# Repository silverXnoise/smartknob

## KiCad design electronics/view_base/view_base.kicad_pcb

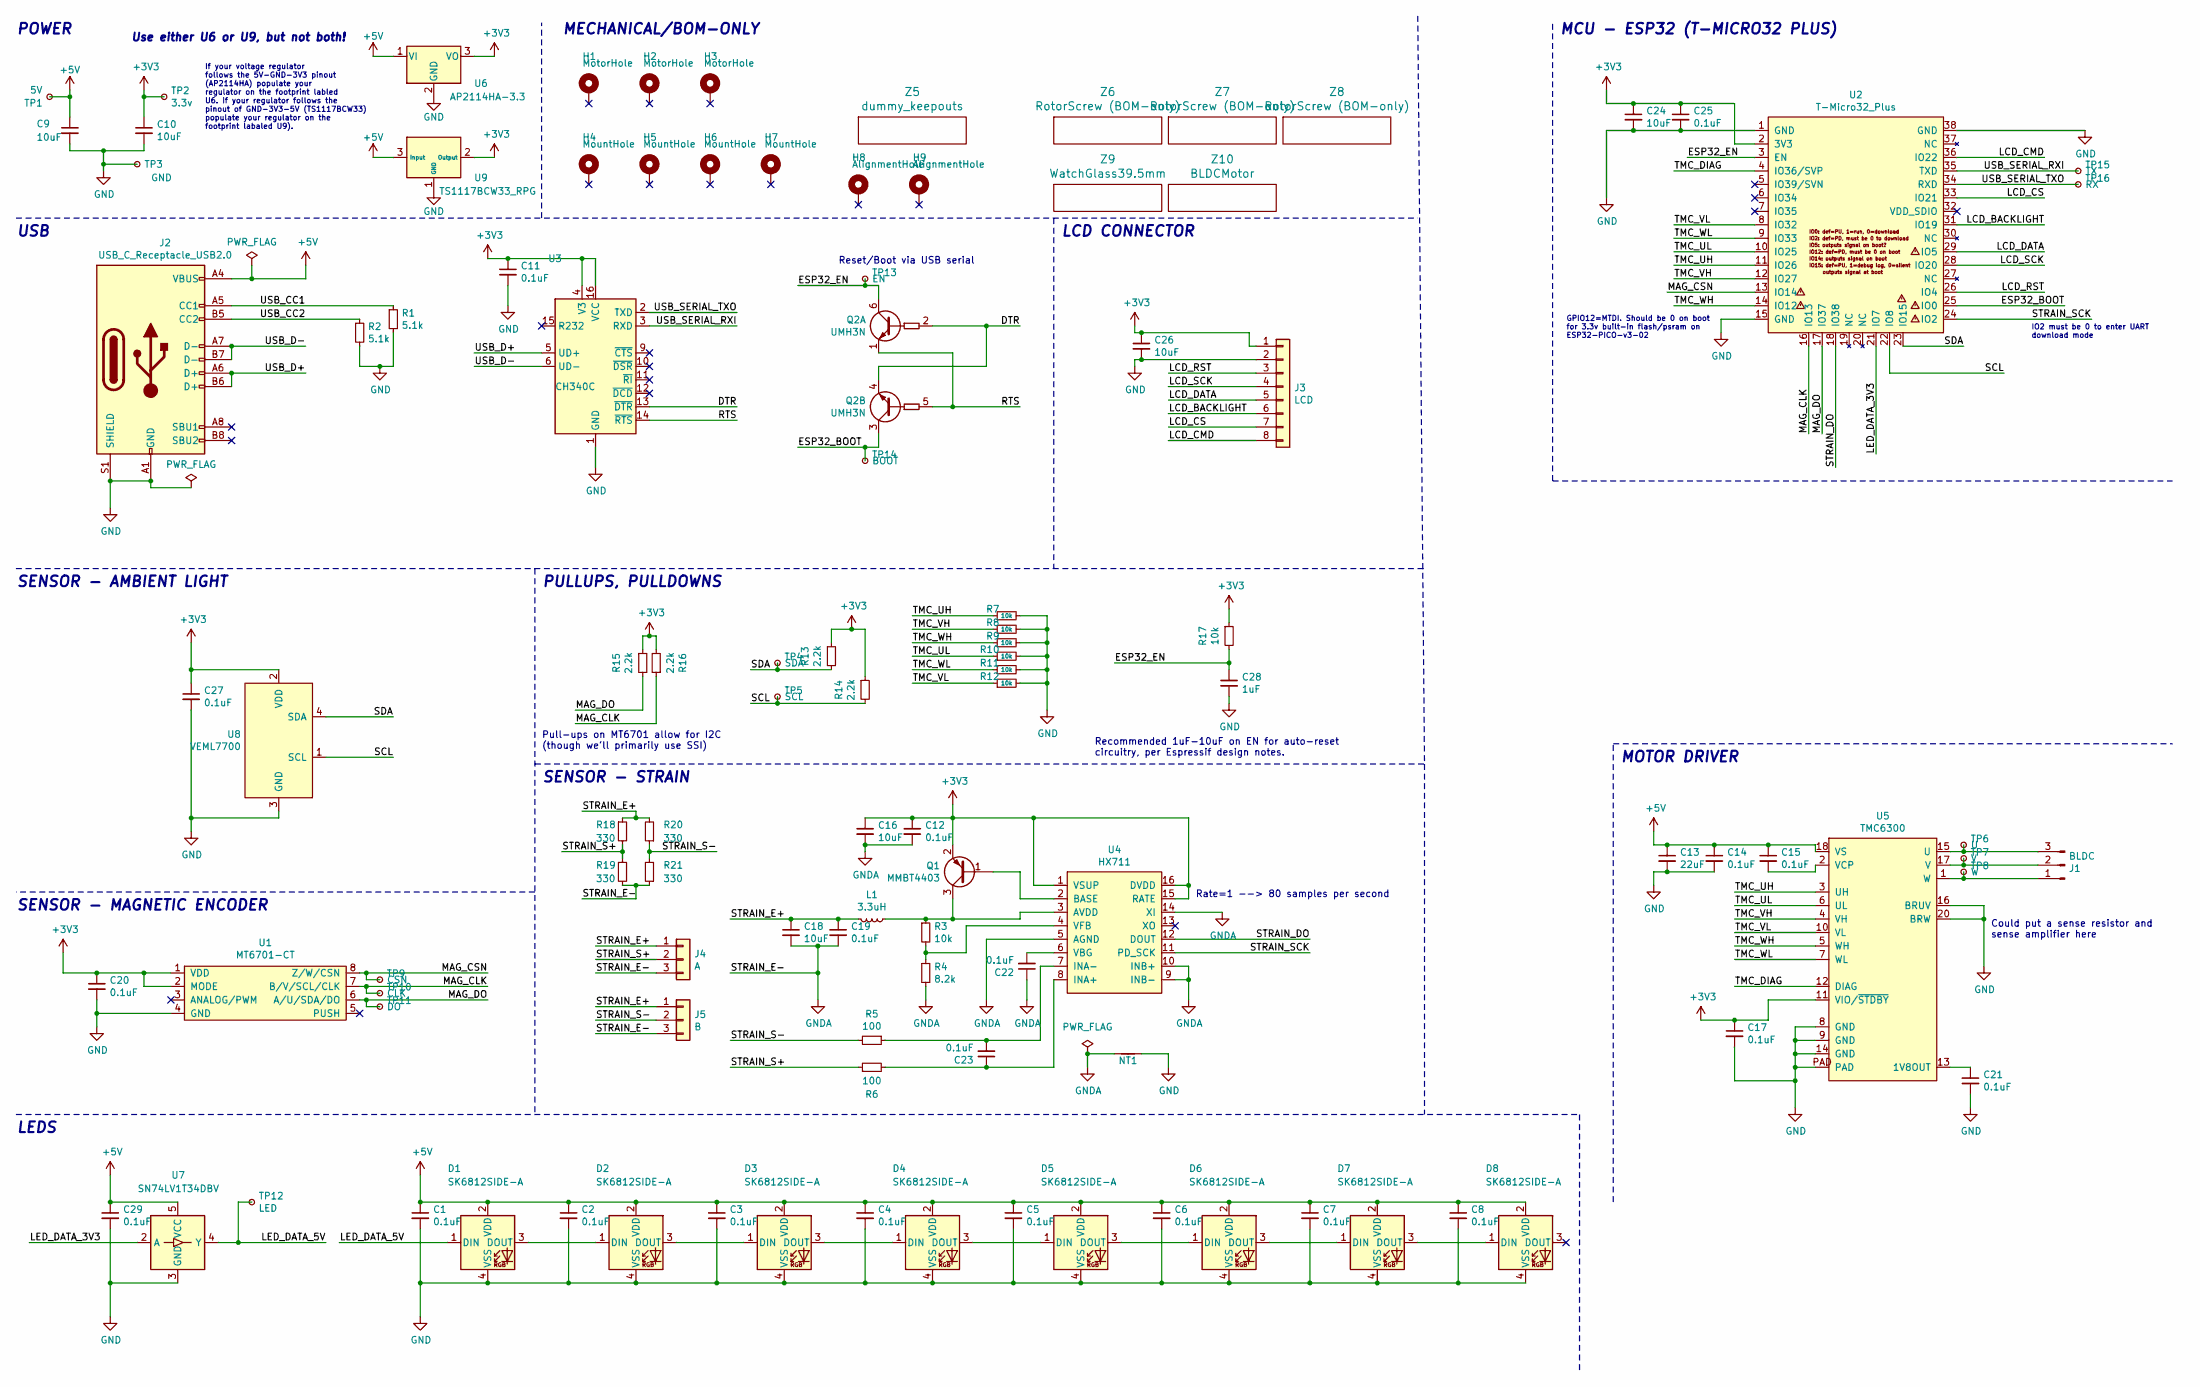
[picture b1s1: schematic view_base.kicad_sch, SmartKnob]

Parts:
C1, C2, C3, C4, C5, C6, C7, C8, C11, C12, C14, C15, C17, C19, C20, C21, C22, C23, C25, C27, C29: 0.1uF; C_0603_1608Metric; LCSC C1591
C9, C10, C16, C18, C24, C26: 10uF; C_0805_2012Metric; LCSC C2922480
C13: 22uF; C_0805_2012Metric; LCSC C98190
C28: 1uF; C_0603_1608Metric; Mouser 187-CL10A105KA8NNNC
D1, D2, D3, D4, D5, D6, D7, D8: SK6812SIDE-A; SK6812-SIDE-A; Digikey 1528-4691-ND
H1, H2, H3: MotorHole; MountingHole_M1.6; LCSC C2931389
H4, H5, H6, H7: MountHole; MountingHole_2.2mm_M2_ISO7380_Pad_NonVirtual; LCSC C2911210 or C2911532 (screw), C2961595 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
H8, H9: AlignmentHole; MountingHole_2.2mm_M2_ISO7380_Pad_NonVirtual
J1: BLDC; 532610371; LCSC C293630
J2: USB_C_Receptacle_USB2.0; USB4510_NoPaste; LCSC C428463
J3: LCD; SolderPads_2mm_8
J4: A; SolderPads_2mm_3_STRAIN
J5: B; SolderPads_2mm_3_STRAIN
L1: 3.3uH; L_0805_2012Metric; LCSC C307744
NT1: NetTie_2; NetTie-2_SMD_Pad0.5mm
Q1: MMBT4403; SOT-23; LCSC C78864
Q2: UMH3N; SOT-363_SC-70-6; LCSC C62892
R1, R2: 5.1k; R_0603_1608Metric; LCSC C105580
R3, R7, R8, R9, R10, R11, R12, R17: 10k; R_0603_1608Metric; LCSC C98220
R4: 8.2k; R_0603_1608Metric; LCSC C114637
R5, R6: 100; R_0603_1608Metric; LCSC C319953
R13, R14, R15, R16: 2.2k; R_0603_1608Metric; LCSC C4190
R18, R19, R20, R21: 330; R_2512_6332Metric; LCSC C19866
TP1: 5V; TestPoint_Pad_D2.0mm_ValueSilk
TP2: 3.3v; TestPoint_Pad_D2.0mm_ValueSilk
TP3: GND; TestPoint_Pad_D2.0mm_ValueSilk
TP4: SDA; TestPoint_Pad_D2.0mm_ValueSilk
TP5: SCL; TestPoint_Pad_D2.0mm_ValueSilk
TP6: U; TestPoint_Pad_D2.0mm_ValueSilk
TP7: V; TestPoint_Pad_D2.0mm_ValueSilk
TP8: W; TestPoint_Pad_D2.0mm_ValueSilk
TP9: CSN; TestPoint_Pad_D2.0mm_ValueSilk
TP10: CLK; TestPoint_Pad_D2.0mm_ValueSilk
TP11: DO; TestPoint_Pad_D2.0mm_ValueSilk
TP12: LED; TestPoint_Pad_D2.0mm_ValueSilk
TP13: EN; TestPoint_Pad_D2.0mm_ValueSilk
TP14: BOOT; TestPoint_Pad_D2.0mm_ValueSilk
TP15: TX; TestPoint_Pad_D2.0mm_ValueSilk
TP16: RX; TestPoint_Pad_D2.0mm_ValueSilk
U1: MT6701-CT; SOIC-8_3.9x4.9mm_P1.27mm; LCSC C2856764, or C3003196
U2: T-Micro32_Plus; T-Micro32; Digikey N/A
U3: CH340C; SOIC-16_3.9x9.9mm_P1.27mm; LCSC C84681
U4: HX711; SOIC-16_3.9x9.9mm_P1.27mm; LCSC C43656
U5: TMC6300; QFN-20-1EP_3x3mm_P0.4mm_EP1.65x1.65mm_ThermalVias_LargerVia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; Digikey TMC6300-LA-T
U6: AP2114HA-3.3; SOT-223-3_TabPin2_InGndOut; LCSC C460314
U7: SN74LV1T34DBV; SOT-23-5; LCSC C100024
U8: VEML7700; VEML7700-TOP; Digikey VEML7700-TT
U9: TS1117BCW33_RPG; SOT-223-3_TabPin2_GndOutIn; LCSC C6186, C35879, or others
Z5: dummy_keepouts; ViewKeepouts3d
Z6, Z7, Z8: RotorScrew (BOM-only); bom_only_no_pin
Z9: WatchGlass39.5mm; bom_only_no_pin
Z10: BLDCMotor; bom_only_no_pin

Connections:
+3V3: C10.1, C11.1, C12.1, C16.1, C17.1, C20.1, C24.1, C25.1, C26.1, C27.1, J3.1, Q1.2 (E), R13.1, R14.1, R15.1, R16.2, R17.1, TP2.1, U1.1 (VDD), U1.2 (MODE), U2.2 (3V3), U3.4 (V3), U3.16 (VCC), U4.1 (VSUP), U4.15 (RATE), U4.16 (DVDD), U5.11 (VIO/~STDBY), U6.3 (VO), U8.2 (VDD), U9.2 (Output)
+5V: C1.1, C2.1, C3.1, C4.1, C5.1, C6.1, C7.1, C8.1, C9.1, C13.1, C14.1, C15.1, C29.1, D1.2 (VDD), D2.2 (VDD), D3.2 (VDD), D4.2 (VDD), D5.2 (VDD), D6.2 (VDD), D7.2 (VDD), D8.2 (VDD), J2.A4 (VBUS), J2.A9 (VBUS), J2.B4 (VBUS), J2.B9 (VBUS), TP1.1, U5.18 (VS), U6.1 (VI), U7.5 (VCC), U9.3 (Input)
/DTR: Q2.2 (B1), Q2.4 (E2), U3.13 (~DTR)
/ESP32_BOOT: Q2.3 (C2), TP14.1, U2.25 (IO0)
/ESP32_EN: C28.1, Q2.6 (C1), R17.2, TP13.1, U2.3 (EN)
/LCD_BACKLIGHT: J3.6, U2.31 (IO19)
/LCD_CMD: J3.8, U2.36 (IO22)
/LCD_CS: J3.7, U2.33 (IO21)
/LCD_DATA: J3.5, U2.29 (IO5)
/LCD_RST: J3.3, U2.26 (IO4)
/LCD_SCK: J3.4, U2.28 (IO20)
/LED_DATA_3V3: U2.21 (IO7), U7.2 (A)
/LED_DATA_5V: D1.1 (DIN), TP12.1, U7.4 (Y)
/MAG_CLK: R16.1, TP10.1, U1.7 (B/V/SCL/CLK), U2.16 (IO13)
/MAG_CSN: TP9.1, U1.8 (Z/W/CSN), U2.13 (IO14)
/MAG_DO: R15.2, TP11.1, U1.6 (A/U/SDA/DO), U2.17 (IO37)
/RTS: Q2.1 (E1), Q2.5 (B2), U3.14 (~RTS)
/SCL: R14.2, TP5.1, U2.22 (IO8), U8.1 (SCL)
/SDA: R13.2, TP4.1, U2.23 (IO15), U8.4 (SDA)
/STRAIN_DO: U2.18 (IO38), U4.12 (DOUT)
/STRAIN_E+: C18.1, C19.1, J4.1, J5.1, L1.2, R18.1, R20.2
/STRAIN_S+: J4.2, R6.1, R18.2, R19.1
/STRAIN_S-: J5.2, R5.2, R20.1, R21.2
/STRAIN_SCK: U2.24 (IO2), U4.11 (PD_SCK)
/TMC_DIAG: U2.4 (IO36/SVP), U5.12 (DIAG)
/TMC_UH: R7.1, U2.11 (IO26), U5.3 (UH)
/TMC_UL: R10.1, U2.10 (IO25), U5.6 (UL)
/TMC_VH: R8.1, U2.12 (IO27), U5.4 (VH)
/TMC_VL: R12.1, U2.8 (IO32), U5.10 (VL)
/TMC_WH: R9.1, U2.14 (IO12), U5.5 (WH)
/TMC_WL: R11.1, U2.9 (IO33), U5.7 (WL)
/USB_CC1: J2.A5 (CC1), R1.1
/USB_CC2: J2.B5 (CC2), R2.1
/USB_D+: J2.A6 (D+), J2.B6 (D+), U3.5 (UD+)
/USB_D-: J2.A7 (D-), J2.B7 (D-), U3.6 (UD-)
/USB_SERIAL_RXI: TP15.1, U2.35 (TXD), U3.3 (RXD)
/USB_SERIAL_TXO: TP16.1, U2.34 (RXD), U3.2 (TXD)
GND: C1.2, C2.2, C3.2, C4.2, C5.2, C6.2, C7.2, C8.2, C9.2, C10.2, C11.2, C13.2, C14.2, C17.2, C20.2, C21.2, C24.2, C25.2, C26.2, C27.2, C28.2, C29.2, D1.4 (VSS), D2.4 (VSS), D3.4 (VSS), D4.4 (VSS), D5.4 (VSS), D6.4 (VSS), D7.4 (VSS), D8.4 (VSS), J2.A1 (GND), J2.A12 (GND), J2.B1 (GND), J2.B12 (GND), J2.S1 (SHIELD), J3.2, NT1.2, R1.2, R2.2, R7.2, R8.2, R9.2, R10.2, R11.2, R12.2, TP3.1, U1.4 (GND), U2.1 (GND), U2.15 (GND), U2.38 (GND), U3.1 (GND), U5.8 (GND), U5.9 (GND), U5.14 (GND), U5.16 (BRUV), U5.20 (BRW), U5.PAD, U6.2 (GND), U7.3 (GND), U8.3 (GND), U9.1 (GND)
GNDA: C12.2, C16.2, C18.2, C19.2, C22.1, J4.3, J5.3, NT1.1, R4.2, R19.2, R21.1, U4.5 (AGND), U4.9 (INB-), U4.10 (INB+), U4.14 (XI)
unnamed: D1.3 (DOUT), D2.1 (DIN)
unnamed: D2.3 (DOUT), D3.1 (DIN)
unnamed: D3.3 (DOUT), D4.1 (DIN)
unnamed: D4.3 (DOUT), D5.1 (DIN)
unnamed: D5.3 (DOUT), D6.1 (DIN)
unnamed: D6.3 (DOUT), D7.1 (DIN)
unnamed: D7.3 (DOUT), D8.1 (DIN)
unnamed: J1.1, TP8.1, U5.1 (W)
unnamed: J1.2, TP7.1, U5.17 (V)
unnamed: J1.3, TP6.1, U5.15 (U)
unnamed: Q1.1 (B), U4.2 (BASE)
unnamed: L1.1, Q1.3 (C), R3.1, U4.3 (AVDD)
unnamed: C23.1, R6.2, U4.8 (INA+)
unnamed: C23.2, R5.1, U4.7 (INA-)
unnamed: C22.2, U4.6 (VBG)
unnamed: R3.2, R4.1, U4.4 (VFB)
unnamed: C21.1, U5.13 (1V8OUT)
unnamed: C15.2, U5.2 (VCP)

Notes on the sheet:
POWER
Could put a sense resistor and sense amplifier here
MCU - ESP32 (T-MICRO32 PLUS)
If your voltage regulator follows the 5V-GND-3V3 pinout (AP2114HA) populate your regulator on the footprint labled U6. If your regulator follows the pinout of GND-3V3-5V (TS1117BCW33) populate your regulator on the footprint labaled U9).
SENSOR - MAGNETIC ENCODER
MOTOR DRIVER
MECHANICAL/BOM-ONLY
IO2 must be 0 to enter UART download mode
GPIO12=MTDI. Should be 0 on boot for 3.3v built-in flash/psram on ESP32-PICO-v3-02
Pull-ups on MT6701 allow for I2C (though we'll primarily use SSI)
Use either U6 or U9, but not both!
Rate=1 --> 80 samples per second
SENSOR - AMBIENT LIGHT
Recommended 1uF-10uF on EN for auto-reset circuitry, per Espressif design notes.
USB
SENSOR - STRAIN
LEDS
PULLUPS, PULLDOWNS
LCD CONNECTOR
Reset/Boot via USB serial

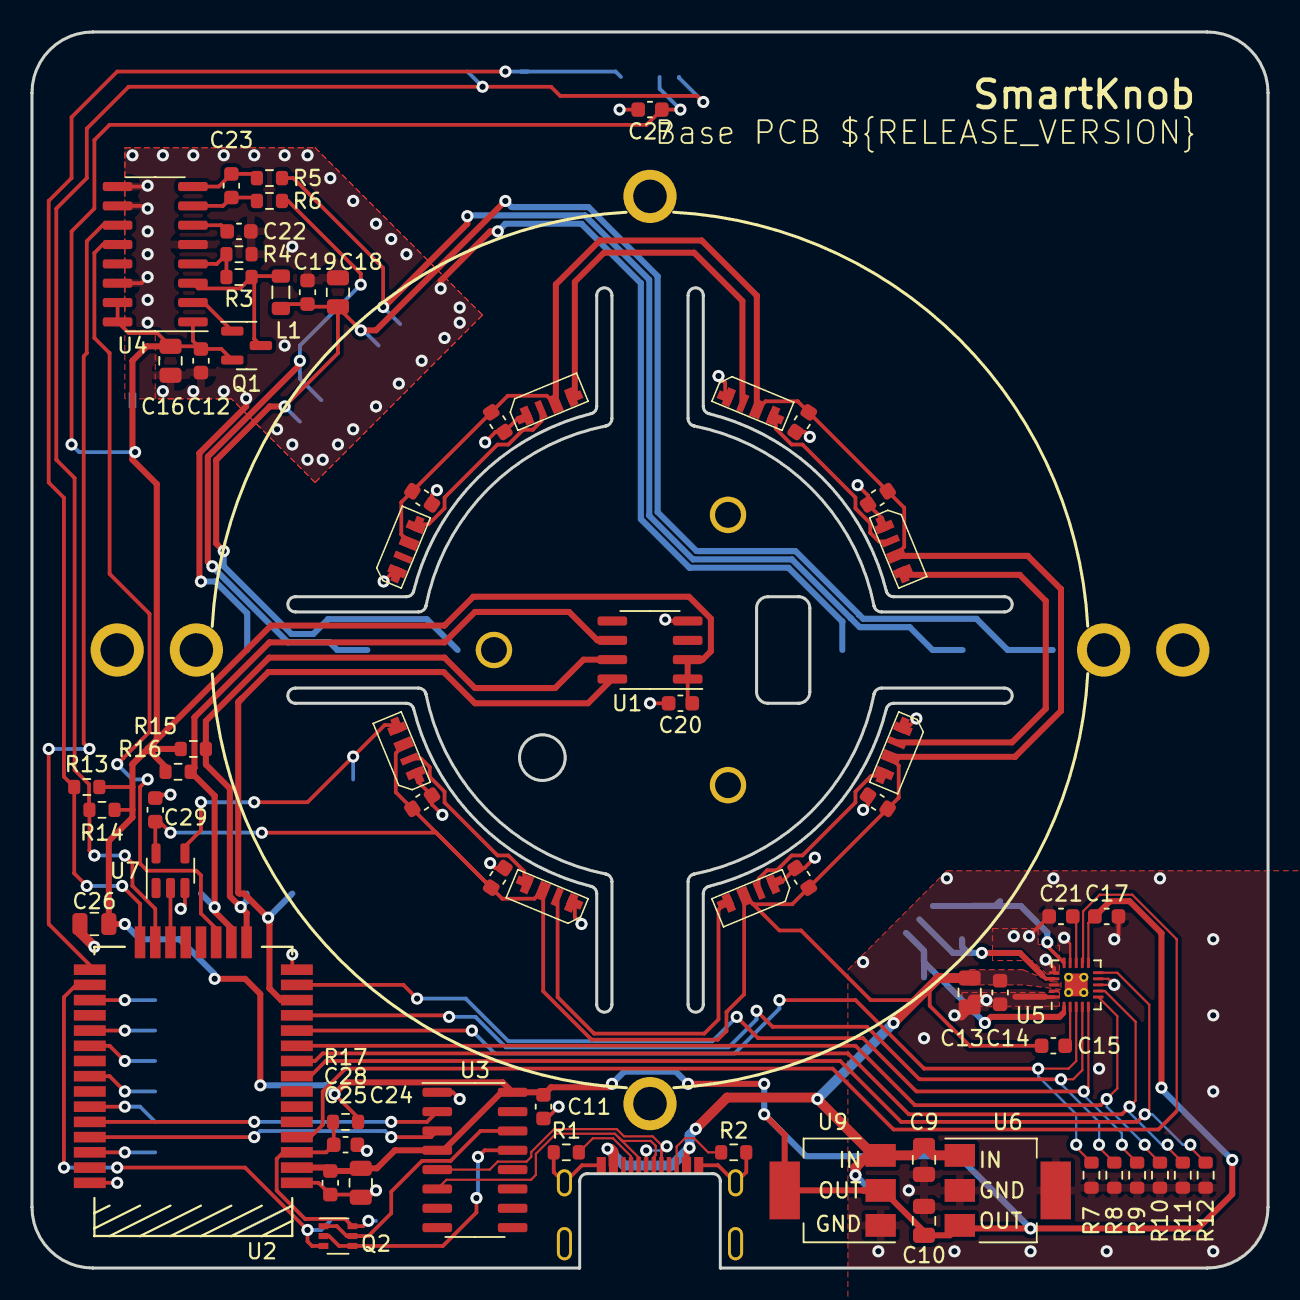
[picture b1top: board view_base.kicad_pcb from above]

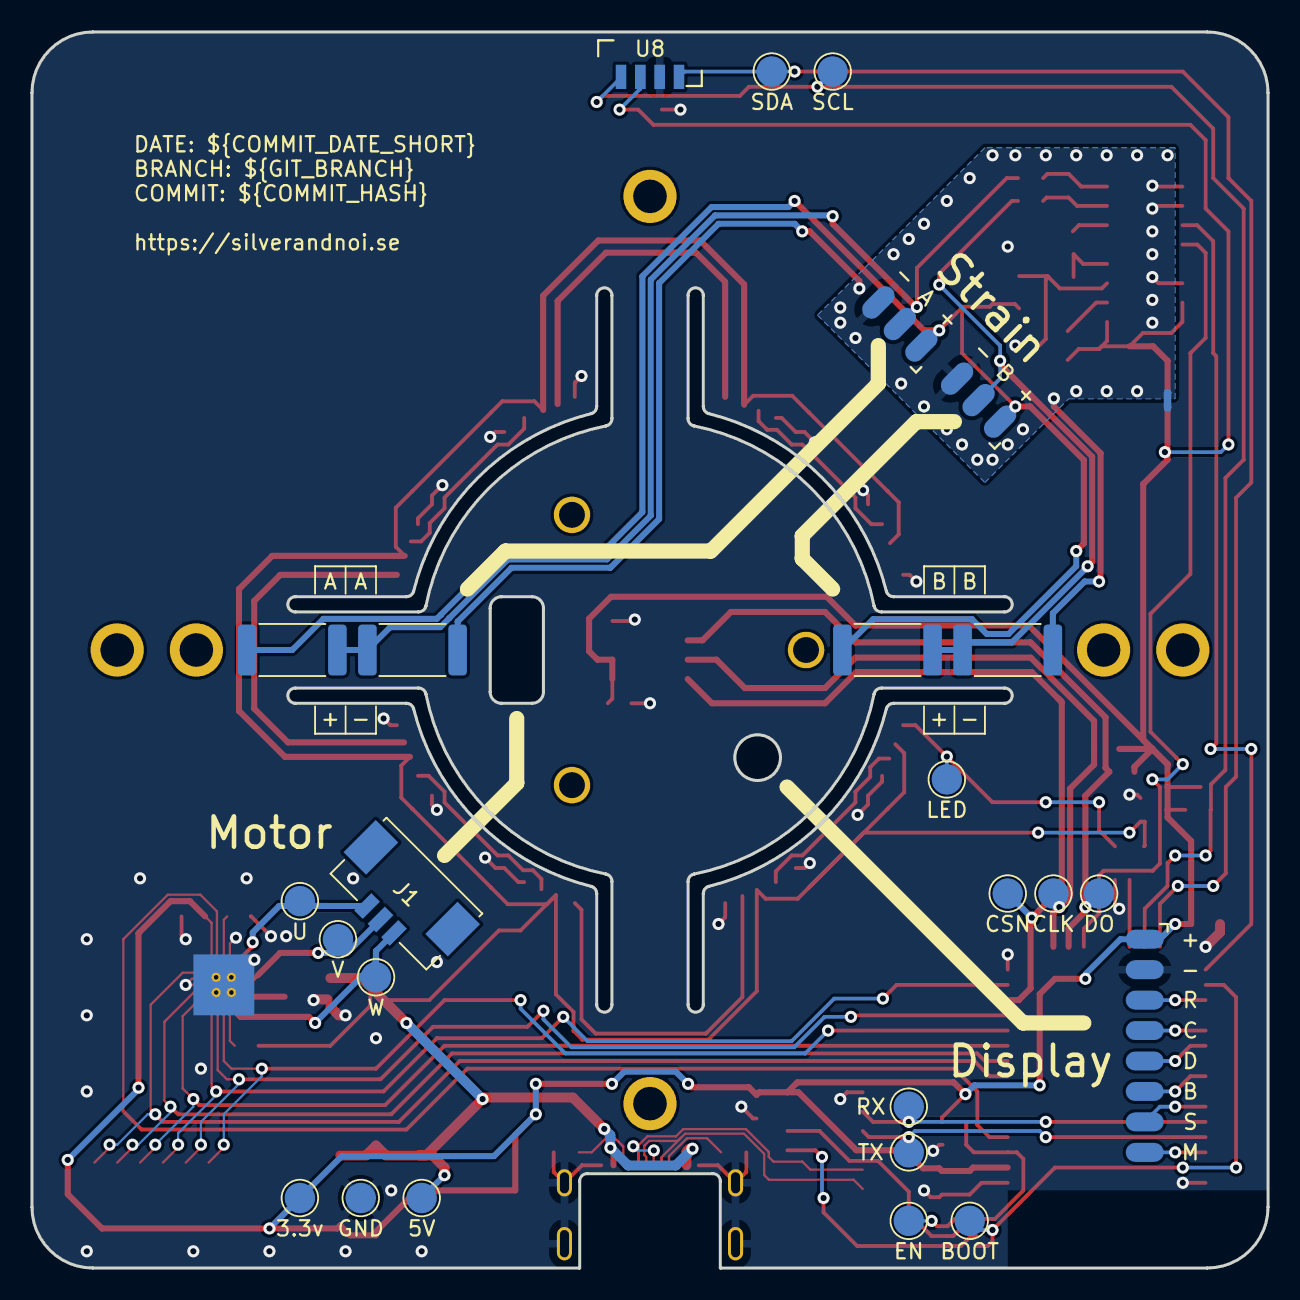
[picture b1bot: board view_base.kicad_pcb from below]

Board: 2 copper layers, 81.2 x 81.2 mm, 107 parts (26 on the bottom side), 57 nets.

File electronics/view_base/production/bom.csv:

Designator,Footprint,Quantity,Value,LCSC Part #
"C1, C11, C12, C14, C15, C17, C19, C2, C20, C21, C22, C23, C25, C27, C29, C3, C4, C5, C6, C7, C8",0603,21,0.1uF,C1591
"C10, C16, C18, C24, C26, C9",0805,6,10uF,C2922480
C13,0805,1,22uF,C98190
C28,0603,1,1uF,C5673
"D1, D2, D3, D4, D5, D6, D7, D8",SK6812-SIDE-A,8,SK6812SIDE-A,C2890037
"H1, H2, H3",MountingHole_M1.6,3,MotorHole,C2931389
"H4, H5, H6, H7",MountingHole_2.2mm_M2_ISO7380_Pad_NonVirtual,4,MountHole,"C2911210 or C2911532 (screw), C2961595 (nut)"
"H8, H9",MountingHole_2.2mm_M2_ISO7380_Pad_NonVirtual,2,AlignmentHole,
J1,532610371,1,BLDC,C293630
J2,USB4510_NoPaste,1,USB_C_Receptacle_USB2.0,C428463
J3,SolderPads_2mm_8,1,LCD,
J4,SolderPads_2mm_3_STRAIN,1,A,
J5,SolderPads_2mm_3_STRAIN,1,B,
L1,0805,1,3.3uH,C307744
Q1,SOT-23,1,MMBT4403,C78864
Q2,SOT-363_SC-70-6,1,UMH3N,C62892
"R1, R2",0603,2,5.1k,C105580
"R10, R11, R12, R17, R3, R7, R8, R9",0603,8,10k,C98220
"R13, R14, R15, R16",0603,4,2.2k,C4190
"R18, R19, R20, R21",2512,4,330,C19866
R4,0603,1,8.2k,C114637
"R5, R6",0603,2,100,C319953
TP1,TestPoint_Pad_D2.0mm_ValueSilk,1,5V,
TP10,TestPoint_Pad_D2.0mm_ValueSilk,1,CLK,
TP11,TestPoint_Pad_D2.0mm_ValueSilk,1,DO,
TP12,TestPoint_Pad_D2.0mm_ValueSilk,1,LED,
TP13,TestPoint_Pad_D2.0mm_ValueSilk,1,EN,
TP14,TestPoint_Pad_D2.0mm_ValueSilk,1,BOOT,
TP15,TestPoint_Pad_D2.0mm_ValueSilk,1,TX,
TP16,TestPoint_Pad_D2.0mm_ValueSilk,1,RX,
TP2,TestPoint_Pad_D2.0mm_ValueSilk,1,3.3v,
TP3,TestPoint_Pad_D2.0mm_ValueSilk,1,GND,
TP4,TestPoint_Pad_D2.0mm_ValueSilk,1,SDA,
TP5,TestPoint_Pad_D2.0mm_ValueSilk,1,SCL,
TP6,TestPoint_Pad_D2.0mm_ValueSilk,1,U,
TP7,TestPoint_Pad_D2.0mm_ValueSilk,1,V,
TP8,TestPoint_Pad_D2.0mm_ValueSilk,1,W,
TP9,TestPoint_Pad_D2.0mm_ValueSilk,1,CSN,
U1,SOIC-8_3.9x4.9mm_P1.27mm,1,MT6701-CT,"C2856764, or C3003196"
U2,T-Micro32,1,T-Micro32_Plus,N/A
U3,SOIC-16_3.9x9.9mm_P1.27mm,1,CH340C,C84681
U4,SOIC-16_3.9x9.9mm_P1.27mm,1,HX711,C43656
U5,QFN-20-1EP_3x3mm_P0.4mm_EP1.65x1.65mm_ThermalVias_LargerViaHoles,1,TMC6300,N/A
U6,SOT-223-3_TabPin2_InGndOut,1,AP2114HA-3.3,C460314
U7,SOT-23-5,1,SN74LV1T34DBV,C100024
U8,VEML7700-TOP,1,VEML7700,C1850416
U9,SOT-223-3_TabPin2_GndOutIn,1,TS1117BCW33_RPG,"C6186, C35879, or others"

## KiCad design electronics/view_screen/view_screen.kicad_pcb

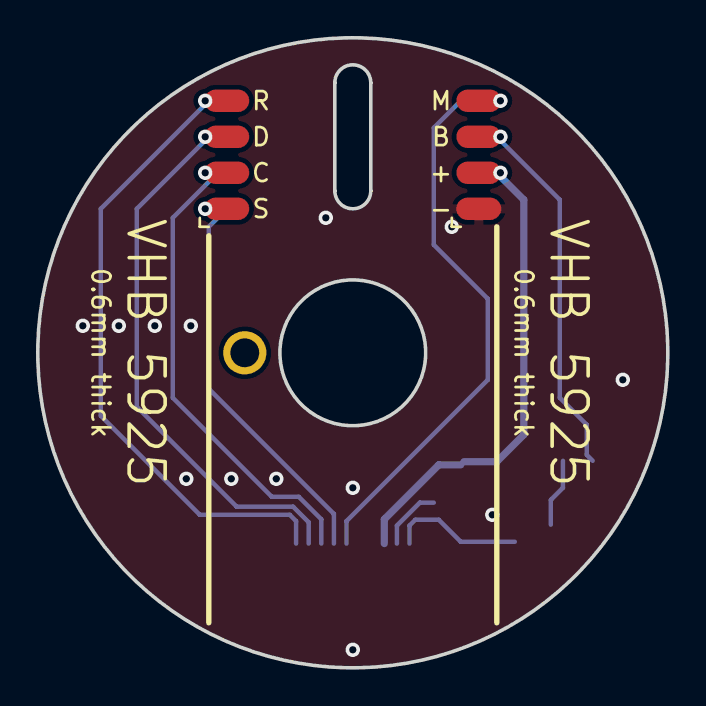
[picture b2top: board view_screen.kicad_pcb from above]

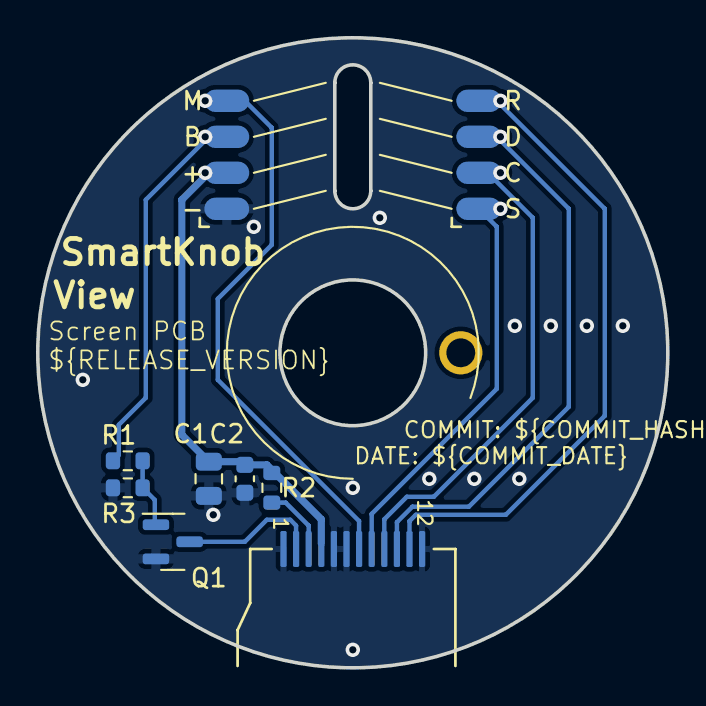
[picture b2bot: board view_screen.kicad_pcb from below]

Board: 2 copper layers, 35.0 x 35.0 mm, 12 parts (9 on the bottom side), 11 nets.

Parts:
C1: 22uF; C_0805_2012Metric
C2: 0.1uF; C_0603_1608Metric
H1: AlignmentHole; AlignmentHole_1.6
J1, J3, J4, J5: Conn_01x04; SolderPads_2mm_4
J2: GC9A01; GC9A01Round1.28
Q1: 2N7002; SOT-23
R1: 10k; R_0603_1608Metric
R2: 22R; R_0603_1608Metric
R3: 1M; R_0603_1608Metric

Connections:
/BACKLIGHT_EN: J1.3, J4.3, R1.1
/DC: J1.4, J2.7, J4.4
/LEDA: J2.3, R2.2
/LEDK: J2.2, Q1.3 (D)
/MOSI: J2.10, J3.3, J5.3
/SCK: J2.9, J3.2, J5.2
/VDD: C1.1, C2.1, J1.2, J2.4, J4.2, R2.1
/nCS: J2.8, J3.1, J5.1
/nRESET: J2.11, J3.4, J5.4
GND: C1.2, C2.2, J1.1, J2.1, J2.5, J2.6, J2.12, J4.1, Q1.2 (S), R3.2
unnamed: Q1.1 (G), R1.2, R3.1

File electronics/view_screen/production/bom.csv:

Designator,Footprint,Quantity,Value,LCSC Part #
C1,0805,1,22uF,C98190
C2,0603,1,0.1uF,C1591
H1,AlignmentHole_1.6,1,AlignmentHole,
"J1, J3, J4, J5",SolderPads_2mm_4,4,Conn_01x04,
J2,GC9A01Round1.28,1,GC9A01,N/A
Q1,SOT-23,1,2N7002,2N7002
R1,0603,1,10k,C98220
R2,0603,1,22R,
R3,0603,1,1M,

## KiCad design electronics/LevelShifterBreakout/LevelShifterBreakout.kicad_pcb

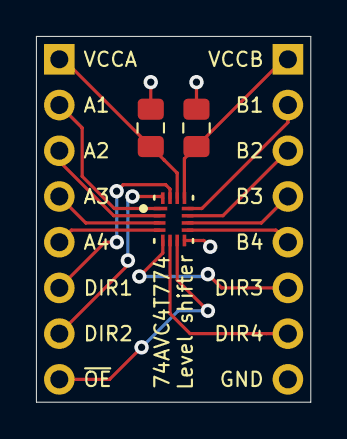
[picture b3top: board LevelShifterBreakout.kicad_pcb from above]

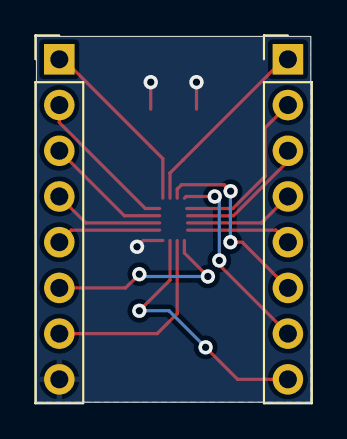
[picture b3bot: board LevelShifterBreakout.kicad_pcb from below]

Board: 2 copper layers, 15.2 x 20.3 mm, 5 parts (2 on the bottom side), 16 nets.

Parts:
C1, C2: 0.1uF; C_0805_2012Metric_Pad1.18x1.45mm_HandSolder
J1, J2: Conn_01x08_Male; PinHeader_1x08_P2.54mm_Vertical
U1: SN74AVC4T774RSVR; Texas_Instruments-RSV_R-PUQFN-N16-0-0-0

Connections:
/A1: J1.2, U1.1
/A2: J1.3, U1.2
/A3: J1.4, U1.3
/A4: J1.5, U1.4
/B1: J2.2, U1.12
/B2: J2.3, U1.11
/B3: J2.4, U1.10
/B4: J2.5, U1.9
/DIR1: J1.6, U1.15
/DIR2: J1.7, U1.16
/DIR3: J2.6, U1.5
/DIR4: J2.7, U1.6
/VCCA: C1.1, J1.1, U1.14
/VCCB: C2.1, J2.1, U1.13
/nOE: J1.8, U1.7
GND: C1.2, C2.2, J2.8, U1.8

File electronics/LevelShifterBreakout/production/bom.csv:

Designator,Footprint,Quantity,Value,LCSC Part #
"C1, C2",0805,2,0.1uF,
"J1, J2",PinHeader_1x08_P2.54mm_Vertical,2,Conn_01x08_Male,
U1,Texas_Instruments-RSV_R-PUQFN-N16-0-0-0,1,SN74AVC4T774RSVR,

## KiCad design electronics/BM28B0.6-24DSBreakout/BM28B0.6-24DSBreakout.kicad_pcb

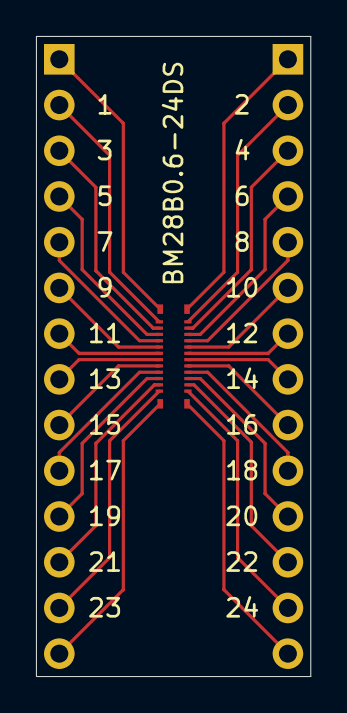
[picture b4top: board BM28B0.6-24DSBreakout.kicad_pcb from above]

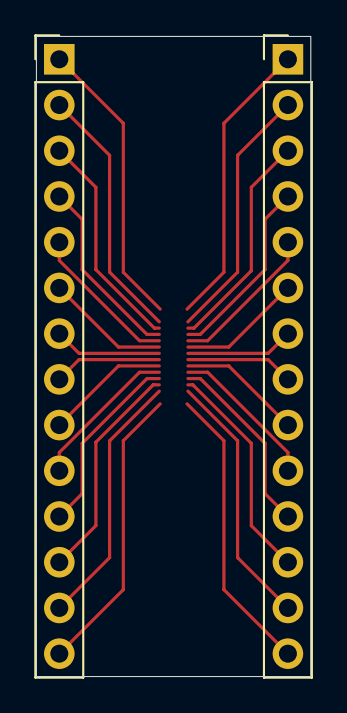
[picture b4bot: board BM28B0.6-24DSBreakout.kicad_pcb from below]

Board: 2 copper layers, 15.2 x 35.6 mm, 3 parts (2 on the bottom side), 28 nets.

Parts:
J1, J2: Conn_01x14_Male; PinHeader_1x14_P2.54mm_Vertical
J3: Conn_02x14_Odd_Even; BM28B0.6-24DS

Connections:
/P25: J1.1, J3.25
/P26: J2.1, J3.26
/P27: J1.14, J3.27
/P28: J2.14, J3.28
unnamed: J1.2, J3.1
unnamed: J1.3, J3.3
unnamed: J1.4, J3.5
unnamed: J1.5, J3.7
unnamed: J1.6, J3.9
unnamed: J1.7, J3.11
unnamed: J1.8, J3.13
unnamed: J1.9, J3.15
unnamed: J1.10, J3.17
unnamed: J1.11, J3.19
unnamed: J1.12, J3.21
unnamed: J1.13, J3.23
unnamed: J2.2, J3.2
unnamed: J2.3, J3.4
unnamed: J2.4, J3.6
unnamed: J2.5, J3.8
unnamed: J2.6, J3.10
unnamed: J2.7, J3.12
unnamed: J2.8, J3.14
unnamed: J2.9, J3.16
unnamed: J2.10, J3.18
unnamed: J2.11, J3.20
unnamed: J2.12, J3.22
unnamed: J2.13, J3.24

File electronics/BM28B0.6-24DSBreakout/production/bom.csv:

Designator,Footprint,Quantity,Value,LCSC Part #
"J1, J2",PinHeader_1x14_P2.54mm_Vertical,2,Conn_01x14_Male,
J3,BM28B0.6-24DS,1,Conn_02x14_Odd_Even,

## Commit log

2023-05-09 Added moldule
2024-09-27 Removed broken module
2024-09-27 Re-added submodule
2024-09-27 Updated project info
2024-09-27 Updated project
2024-09-27 Updated project vars
2024-09-27 Added branch var view_base.kicad_pcb and view_base.kicad_pro
2024-09-27 Generated gerbers
2024-10-25 Added gerbers and img

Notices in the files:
parts and their libraries:
Copyright 2021 Accelerated Designs. All rights reserved.
